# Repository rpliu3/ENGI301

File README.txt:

Repository for ENGI301 course work

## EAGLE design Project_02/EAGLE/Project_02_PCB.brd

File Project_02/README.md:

## PCB Design for Multi-Fandom Kpop Fan Light Display with Music

This project aims to design a PCB for the project completed in Project_01. The PCB will contain key components such as the PocketBeagle, buttons, USB connection for the audio dongle, level shifter to stabilize the signal going to the LED strip, and 3 pin 100 mil header connection for the LED strip. 

The PCB will be integrated with the LED strip and audio components from Project_01, and will maintain the same overall functions. The buttons will still serve as the user interface and have the same functions associated with them.

The docs folder contains the project proposal, Gerber views, schematics PDF, and BOM.

All files needed to create the PCB are contained in the Eagle sub-folder. 

Finally, the MFG folder contains the original Gerber files and CAM outputs.

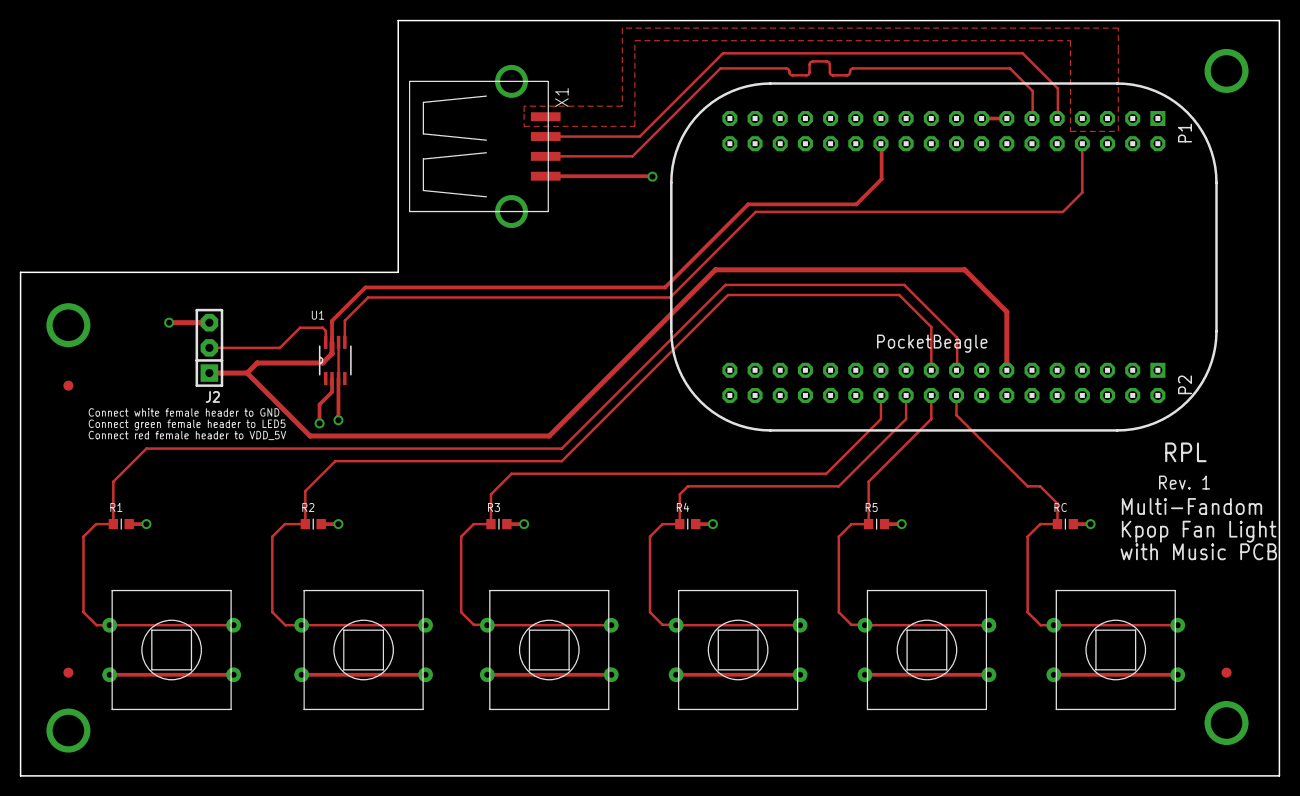
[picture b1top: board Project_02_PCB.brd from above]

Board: 4 copper layers, 127.0 x 76.2 mm, 23 parts (0 on the bottom side), 14 nets.

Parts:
FUD1, FUD2, FUD3: FIDUCIAL; FIDUCIAL_40MIL
J2: F-1X03-SIP-100-32; SIP-100-03-32
MGT1, MGT2, MGT3, MGT4: MOUNTING_HOLE
R1, R2, R3, R4, R5: 1.5k; R0603
RC: 1.5k; R0603
U1: TXS0102DCTT; SOP65P400X130-8N
U$1, U$2, U$3, U$4, U$6, U$7: BUTTON
U$5: POCKETBEAGLE
X1: USB-A-S

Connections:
BUTTON1: R1.1, U$1.P$1, U$1.P$3, U$5.17@P2
BUTTON2: R2.1, U$2.P$1, U$2.P$3, U$5.19@P2
BUTTON3: R3.1, U$5.24@P2, U$7.P$1, U$7.P$3
BUTTON4: R4.1, U$5.22@P2, U$6.P$1, U$6.P$3
BUTTON5: R5.1, U$4.P$1, U$4.P$3, U$5.20@P2
BUTTONC: RC.1, U$3.P$1, U$3.P$3, U$5.18@P2
DN: U$5.9@P1, X1.D-
DP: U$5.11@P1, X1.D+
GND: J2.3, MGT1.P$1, MGT2.P$1, MGT3.P$1, MGT4.P$1, U1.2, U$1.P$2, U$1.P$4, U$2.P$2, U$2.P$4, U$3.P$2, U$3.P$4, U$4.P$2, U$4.P$4, U$5.13@P1, U$5.15@P1, U$5.15@P2, U$5.16@P1, U$5.21@P2, U$5.22@P1, U$6.P$2, U$6.P$4, U$7.P$2, U$7.P$4, X1.GND
LED3: U1.5, U$5.8@P1
LED5: J2.2, U1.8
VDD_3P3V: R1.2, R2.2, R3.2, R4.2, R5.2, RC.2, U1.3, U1.6, U$5.14@P1
VDD_5V: J2.1, U1.7, U$5.13@P2, U$5.24@P1
VUSB: U$5.5@P1, U$5.7@P1, X1.VBUS

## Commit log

2019-09-19 Updating README.md
2019-09-19 no message
2019-10-08 simple calculator done in class
2019-10-08 support for operators: right shift, left shift, modulo, exponentiation
2019-10-08 add support for python 2
2019-10-08 changed input type from float to integer so that it can be used with right and left shift
2019-10-08 fixed issues with indent error
2019-10-08 remove file
2019-10-08 renamed for consistency, added contact info to header
2019-10-08 edited header
2019-10-08 created program to blink USR3 LED at 5 Hz on beaglebone
2019-10-08 closed comment block
2019-11-06 create file for project 1 code
2019-11-06 upload proposal
2019-11-17 updated components in block diagrams and parts list
2019-11-17 Revert "updated components in block diagrams and parts list"
    This reverts commit 77fea194e4a299eabf5395fb2c17f7a6271ef473.
2019-11-17 remove old project proposal
2019-11-17 remove old project code file
2019-11-17 updated block diagrams and parts list
2019-11-17 Revert "remove old project code file"
    This reverts commit 1a77e61e192cc2f2128580228551e638069933e0.
2019-11-17 Revert "remove old project proposal"
    This reverts commit e8ab108026ee6f7ef8709e5b6da7e8cfb493862f.
2019-11-17 commented and cleaned up code for audio and user interface aspects of project
2019-11-17 removed old project proposal
2019-11-17 create README.md file for project 01 repository
2019-11-17 created heading
2019-11-17 edited parts list
2019-11-17 added build and operation instructions for audio and control portion
2019-11-17 edited button variable for consistency
2019-11-17 edited typo
2019-11-19 included LED lights information
2019-11-19 remove old code file
2019-11-19 create test file for audio component
2019-11-19 create final composite code for project
2019-11-19 create test for light component of project
2019-11-19 updated building and usage to include LEDs
2019-11-19 create custom configure file for HKBAYI 240 pixels programmable RGB LED Strip
2019-11-19 added Hackster link
2019-11-19 moved code files to code folder
2019-11-26 project 2 proposal
2019-11-26 remove proposal
2019-11-26 Create Project_02
2019-11-26 create project 2 proposal
2019-11-26 move proposal to docs subfolder
2019-12-17 create board for PCB
2019-12-17 create schematics for PCB
2019-12-21 Remove old proposal
2019-12-21 Updated project proposal
2019-12-21 screenshot of bottom layer of Gerber file
2019-12-21 screenshot of top view of Gerber files
2019-12-21 create BOM
2019-12-21 create PDF of schematics
2019-12-21 shifted section title for header
2019-12-21 moved library into folder
2019-12-21 updated schematic
2019-12-21 CAM outputs
2019-12-21 Generate Gerber files
2019-12-21 move Gerber files to MFG folder
2019-12-21 updated BOM
2019-12-21 rename BOM
